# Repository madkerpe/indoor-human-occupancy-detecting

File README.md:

# Indoor Human Detection & Localisation using Thermal Sensors

This repository contains all the code for the "Cross-Course Project" for the bachelor computer science @Ugent.
We looked into the possibility of tracking humans indoor with relatively new cheap thermal sensors.

This was a group project, my main contributions were:
* Writing the embedded software
* Designing the PCB for the thermal sensors
* Programming the kalman filters to track people in the room.
* Making the poster below

### Calibration

### Processing stack

### More than one person

### One person, multiple sensors

### Multiple people, multiple sensors

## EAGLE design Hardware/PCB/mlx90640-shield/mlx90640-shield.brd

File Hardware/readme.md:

POST request to <server-ip>

JSON:<br>
{<br>
    "device_id": <device_id>,<br>
    "sequence": <sequence_id>,<br>
    "data": <array with size 32x24><br>
}

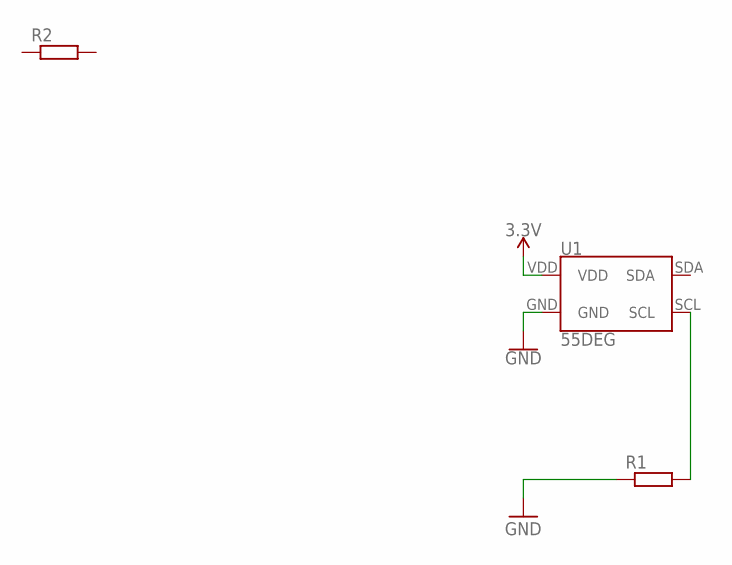
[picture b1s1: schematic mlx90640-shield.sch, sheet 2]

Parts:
R1: R-EU_0204/2V; 0204V
R2: R-EU_0207/7; 0207/7
U1: 55DEG; MLX90540_MLX90640

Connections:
3.3V: U1.VDD
GND: R1.1, U1.GND
unnamed: R1.2, U1.SCL

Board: 2 copper layers, 3 parts (0 on the bottom side), 2 nets, no tracks yet.

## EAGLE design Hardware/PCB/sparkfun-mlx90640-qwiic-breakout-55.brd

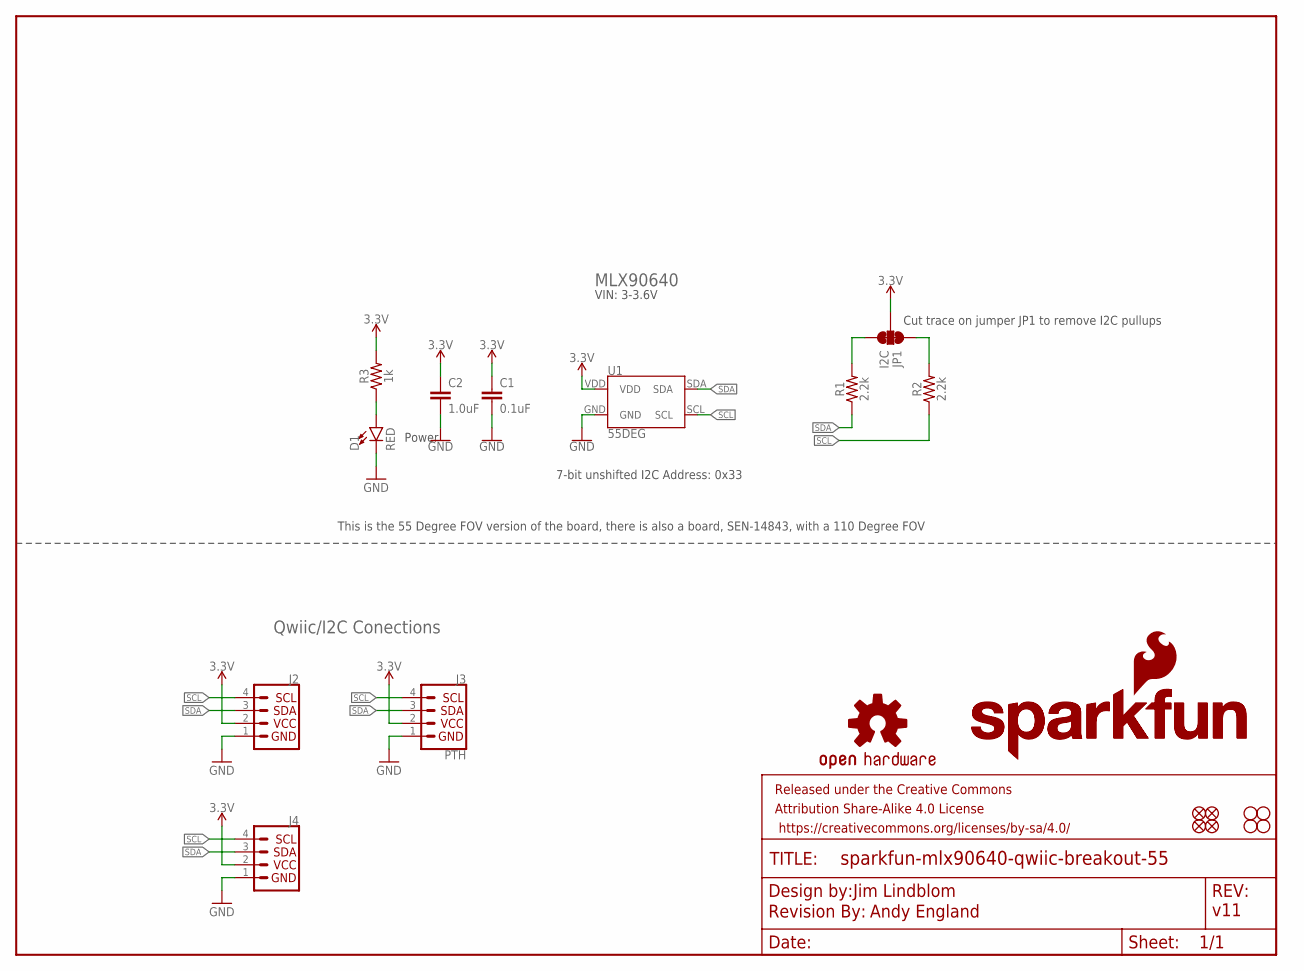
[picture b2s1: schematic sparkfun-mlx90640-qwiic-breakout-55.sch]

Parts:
C1: 0.1uF; 0603
C2: 1.0uF; 0603
D1: RED; LED-0603
FRAME1: FRAME-LETTER; CREATIVE_COMMONS
J2, J4: QWIIC_CONNECTORJS-1MM; 1X04_1MM_RA
J3: PTH; 1X04_NO_SILK
JP1: I2C; SMT-JUMPER_3_2-NC_TRACE_NO-SILK
JP2, JP5, JP6, JP7: FIDUCIALUFIDUCIAL; MICRO-FIDUCIAL
JP3, JP4, JP8, JP9: STAND-OFF
LOGO1: OSHW-LOGOMINI; OSHW-LOGO-MINI
LOGO2: SFE_LOGO_NAME_FLAME.1_INCH; SFE_LOGO_NAME_FLAME_.1
LOGO3: SFE_LOGO_NAME.1_INCH; SFE_LOGO_NAME_.1
LOGO4: REVISION
R1, R2: 2.2k; 0603
R3: 1k; 0603
U1: 55DEG; MLX90540_MLX90640

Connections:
3.3V: C1.1, C2.1, J2.2, J3.2 (VCC), J4.2, JP1.2, R3.2, U1.VDD
GND: C1.2, C2.2, D1.C, J2.1, J3.1 (GND), J4.1, U1.GND
unnamed: JP1.3, R1.2
unnamed: JP1.1, R2.2
unnamed: D1.A, R3.1
SCL: J2.4, J3.4 (SCL), J4.4, R2.1, U1.SCL
SDA: J2.3, J3.3 (SDA), J4.3, R1.1, U1.SDA

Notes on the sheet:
Power
Jim Lindblom
7-bit unshifted I2C Address: 0x33
v11
Andy England
MLX90640
Qwiic/I2C Conections
VIN: 3-3.6V
This is the 55 Degree FOV version of the board, there is also a board, SEN-14843, with a 110 Degree FOV
Cut trace on jumper JP1 to remove I2C pullups

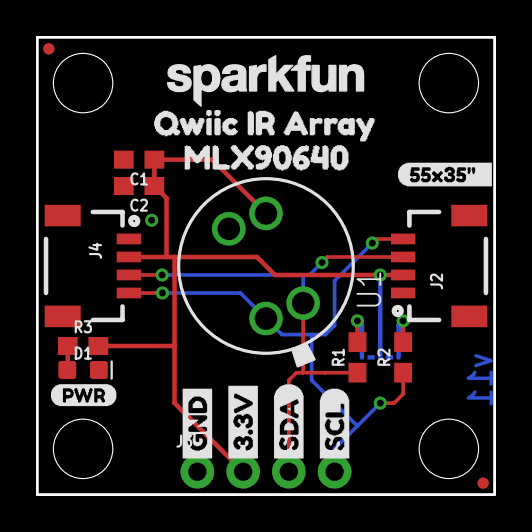
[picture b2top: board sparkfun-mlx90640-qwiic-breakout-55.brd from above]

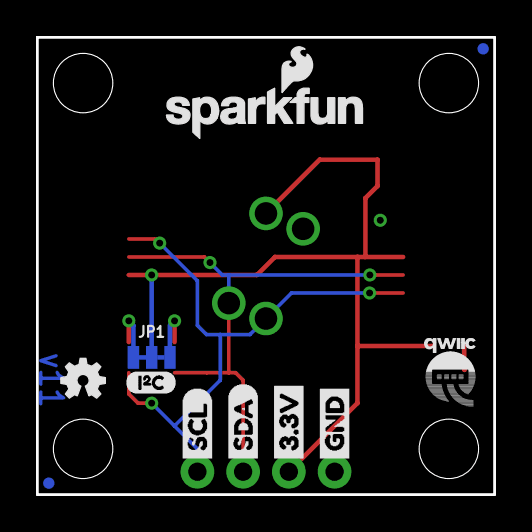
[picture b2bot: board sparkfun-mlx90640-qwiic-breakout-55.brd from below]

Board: 2 copper layers, 25.4 x 25.4 mm, 38 parts (11 on the bottom side), 7 nets.

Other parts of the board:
U$1, U$7: SDA-[)
U$2: 55X35#__0
U$4, U$8: SCL-[)
U$5, U$9: 3.3V
U$6, U$10: GND-04
U$11: QWIIC-LOGO-SMALL
U$12: PWR-()-03
U$13: MLX906401
U$14: QWIIC_IR_ARRAY0
U$16: I_SUPER2_C-()-03

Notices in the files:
parts and their libraries:
SparkFun-IC-Special-Function: Licensing: Creative Commons ShareAlike 4.0 International - https://creativecommons.org/licenses/by-sa/4.0
SparkFun-Aesthetics: Released under the Creative Commons Attribution Share-Alike 4.0 License
SparkFun-Aesthetics: https://creativecommons.org/licenses/by-sa/4.0
